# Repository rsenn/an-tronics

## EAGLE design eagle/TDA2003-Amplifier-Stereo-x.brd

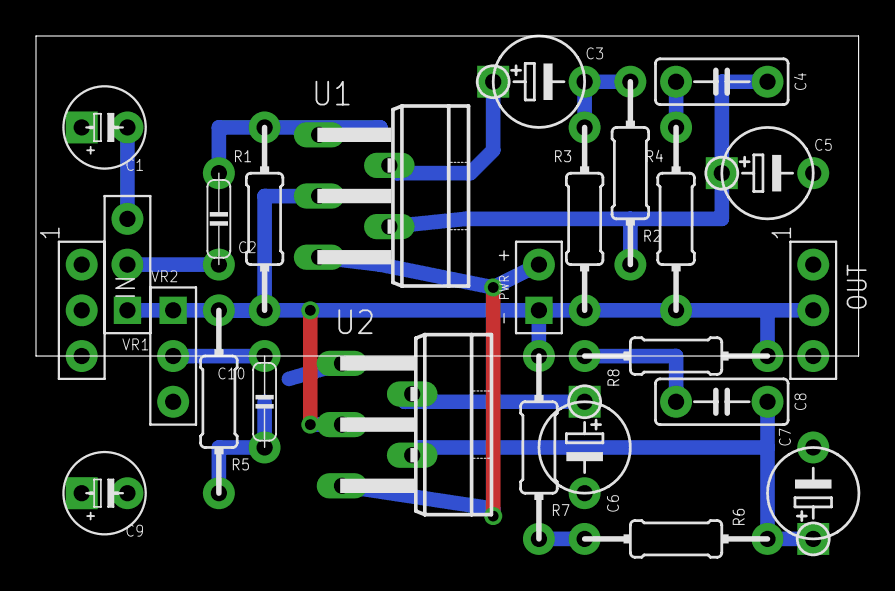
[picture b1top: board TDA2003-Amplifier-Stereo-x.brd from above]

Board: 2 copper layers, 25 parts (0 on the bottom side), 20 nets.

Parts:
C1, C9: 1µF/16V; E2,5-4
C2, C10: 100nF; C050-020X044/V
C3, C6: 220µF/16V; E5-5
C4, C8: 10nF; C050-025X075/V
C5, C7: 1000µF/16V; E5-5
IN: SAUDIO; SPAD-3
OUT: SAUDIO; SPAD-3
PWR: VCC_GNDL; SPAD-+
R1, R5: 100kΩ; 0204/10-V
R2, R6: 220Ω; 0204/10-V
R3, R7: 2.2Ω; 0204/10-V
R4, R8: 1Ω; 0204/10-V
U1, U2: TDA2003-B; TO220-B5
VR1, VR2: 10kΩ; CONN-3P

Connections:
AOUT: C4.1, C5.+, R2.1, U1.4
AOUT1: C7.+, C8.1, R6.1, U2.4
FB: C3.-, R2.2, R3.1
FB1: C6.-, R6.2, R7.1
GND: IN.2, OUT.2, PWR.1, R1.2, R3.2, R4.2, R5.2, R7.2, R8.2, U1.3, U2.3, VR1.1, VR2.1
IN+: C2.2, R1.1, U1.1
IN+1: C10.2, R5.1, U2.1
IN-: C3.+, U1.2
IN-1: C6.+, U2.2
unnamed: C4.2, R4.1
unnamed: C2.1, VR1.2
unnamed: C1.-, VR1.3
unnamed: C1.+, IN.1
unnamed: C8.2, R8.1
unnamed: C9.-, VR2.3
unnamed: C10.1, VR2.2
unnamed: C9.+, IN.3
OUT: C5.-, OUT.1
OUT1: C7.-, OUT.3
VCC: PWR.2, U1.5, U2.5

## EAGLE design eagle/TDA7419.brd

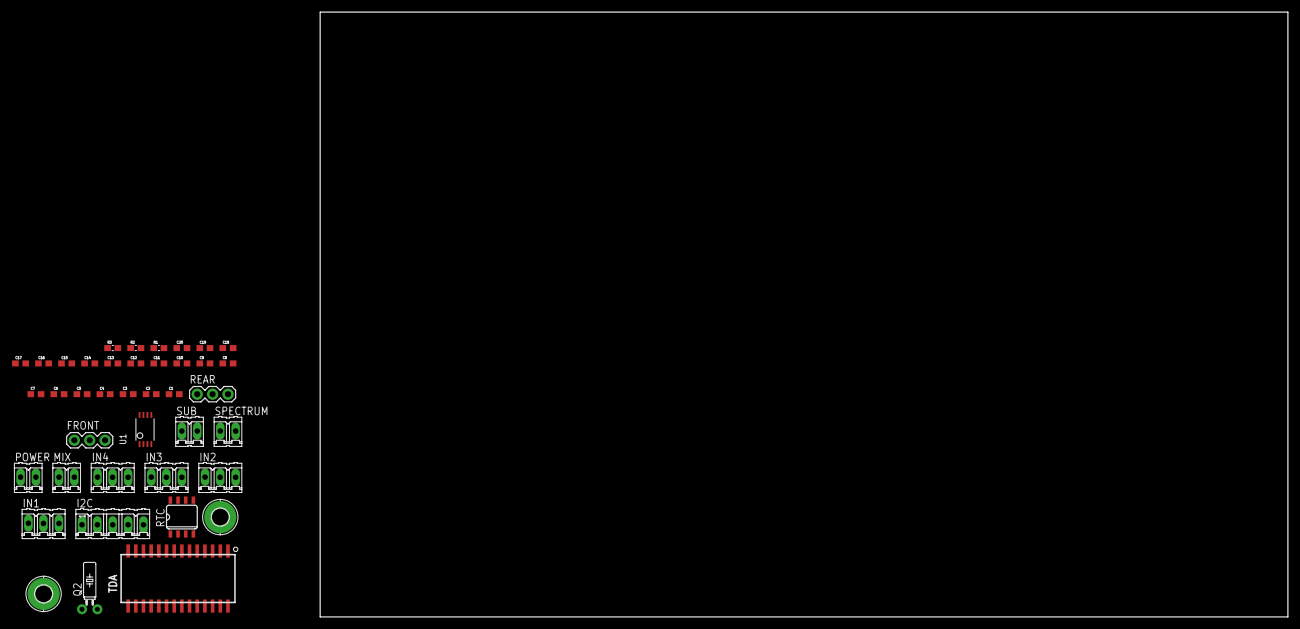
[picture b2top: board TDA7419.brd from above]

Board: 2 copper layers, 160.0 x 100.0 mm, 40 parts (0 on the bottom side), 46 nets, no tracks yet.

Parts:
C1, C13: 10uf; 0603-CAP
C2, C3, C4, C5, C6, C7, C8, C9, C10, C14: 100nf; 0603-CAP
C11, C12: 470nf; 0603-CAP
C15, C16, C17, C18, C19: 4.7uf; 0603-CAP
C20: 8.2pf; 0603-CAP
FRONT: 1X03
H1, H2: MOUNT-PAD-ROUND2.8; 2,8-PAD
I2C: 05P
IN1, IN2, IN3, IN4: 03P
MIX: 02P
POWER: 02P
Q2: TC26HEZ
R1, R2, R3: 10kΩ; 0603-RES
REAR: 1X03
RTC: DS1307SO8-TIGHT; SO08-TIGHT
SPECTRUM: 02P
SUB: 02P
TDA: TDA7419; SOIC-28
U1: TXS0102EPWR; TSSOP8

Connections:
3V3: I2C.4, R1.2, RTC.8, U1.3, U1.7
3VSCL: RTC.6, TDA.22, U1.8
3VSDA: RTC.5, TDA.23, U1.4
5V: I2C.2, R2.2, R3.2, U1.6
5VSCL: I2C.3, R2.1, U1.5
5VSDA: I2C.1, R3.1, U1.1
9V: C13.1, C14.1, C20.1, POWER.1, TDA.24
ACINL: C11.2, TDA.3
ACINR: C12.2, TDA.2
ACOUTL: C11.1, TDA.4
ACOUTR: C12.1, TDA.1
CREF: C1.1, TDA.14
DIFFG: IN4.2, TDA.12
DIFFL: C3.2, TDA.11
DIFFR: C2.2, TDA.13
GND: C1.2, C13.2, C14.2, C20.2, FRONT.2, H1.B2,8, H2.B2,8, I2C.5, IN1.2, IN2.2, IN3.2, MIX.2, POWER.2, R1.1, REAR.2, RTC.3, RTC.4, SUB.2, TDA.15, TDA.27, U1.2
MIX: C10.2, TDA.28
unnamed: C10.1, MIX.1
unnamed: C9.1, IN3.3
unnamed: C8.1, IN3.1
unnamed: C7.1, IN2.3
unnamed: C6.1, IN2.1
unnamed: C5.1, IN1.3
unnamed: C4.1, IN1.1
unnamed: C3.1, IN4.3
unnamed: C2.1, IN4.1
unnamed: C18.1, FRONT.1
unnamed: C17.1, FRONT.3
unnamed: C16.1, REAR.1
unnamed: C15.1, REAR.3
unnamed: C19.1, SUB.1
unnamed: Q2.2, RTC.2
unnamed: Q2.1, RTC.1
OUTLF: C17.2, TDA.20
OUTLR: C15.2, TDA.19
OUTRF: C18.2, TDA.17
OUTRR: C16.2, TDA.18
OUTSW: C19.2, TDA.16
SACLK: SPECTRUM.1, TDA.25
SAOUT: SPECTRUM.2, TDA.26
SE1L: C5.2, TDA.9
SE1R: C4.2, TDA.10
SE2L: C7.2, TDA.7
SE2R: C6.2, TDA.8
SE3L: C9.2, TDA.5
SE3R: C8.2, TDA.6

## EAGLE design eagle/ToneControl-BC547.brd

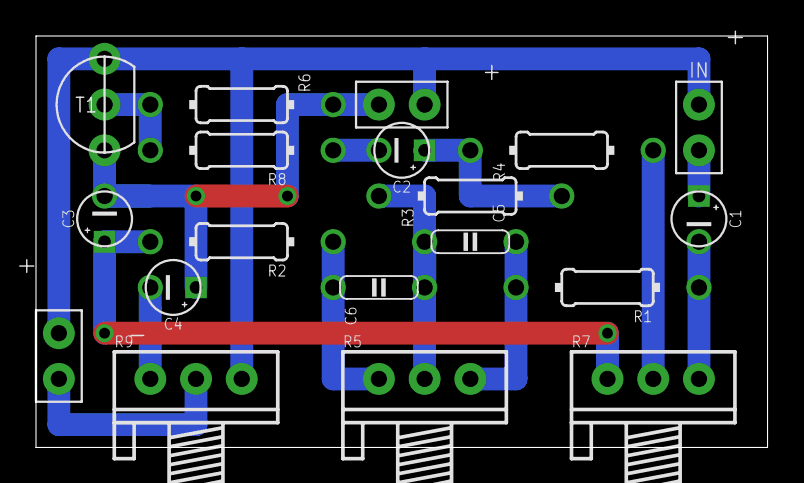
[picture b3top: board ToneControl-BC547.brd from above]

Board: 2 copper layers, 40.6 x 22.9 mm, 19 parts (0 on the bottom side), 14 nets.

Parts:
C1, C3, C4: 3.3μF; E2,5-3
C2: E2,5-3
C5, C6: 100nF; C050-020X044/V
IN: SPAD-+
OUT: SPAD+-
R1, R2: 4.7kΩ; 0204/10
R3: 2.2kΩ; 0204/10-V
R4: 1kΩ; 0204/10-V
R5, R7: 100kΩ; POT
R6: 330kΩ; 0204/10-V
R8: 1kΩ; 0204/10
R9: 20kΩ; POT
S1: VCC_GNDR; SPAD+-
T1: BC547; TO92-CBE

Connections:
GND: IN.1, OUT.1, R9.E, S1.1, T1.E
unnamed: C5.1, R1.2, R5.E
unnamed: C6.1, R2.1, R5.A
unnamed: C5.2, C6.2, R3.1, R5.S
unnamed: C2.+, R3.2, R4.1
unnamed: R4.2, R7.S
unnamed: C2.-, R8.1
unnamed: C3.+, R2.2, R7.A
unnamed: R6.2, R8.2, T1.B
unnamed: C4.-, R9.A
unnamed: C1.-, R1.1, R7.E
unnamed: C1.+, IN.2
unnamed: OUT.2, R9.S
VCC: C3.-, C4.+, R6.1, S1.2, T1.C

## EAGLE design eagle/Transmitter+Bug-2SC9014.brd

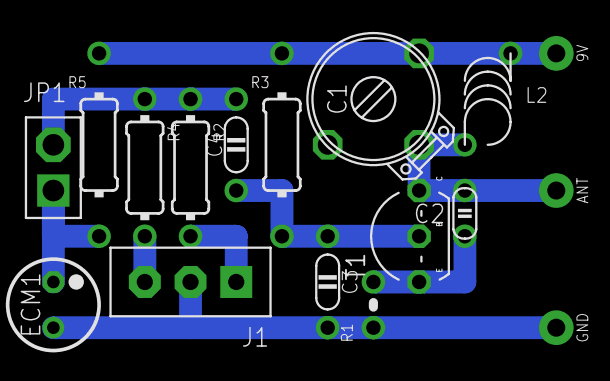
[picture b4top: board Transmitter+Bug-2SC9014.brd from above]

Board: 2 copper layers, 17 parts (0 on the bottom side), 9 nets.

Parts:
9V: SPAD
ANT: ANT; SPAD
C1: 1.6-15pF; TRIM-2222-808
C2: 4.7pF; C025-015X024
C3: 1nF; C050-020X036/V
C4: 10nF; C050-020X036/V
ECM1: ECM-5
GND: SPAD
J1: CONN-3P-3P; CONN-3P
JP1: CONN-2P2P/V; CONN-2P-V
L2: 1uH; L-04-2/5V-X
R1: 100; 0204/2V
R2, R4: 47k; 0204/7-V
R3: 10k; 0204/10-V
R5: 4.7k; 0204/10-V
T1: 2SC9014; TO92-EBC

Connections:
+UB: 9V.1, C1.3, L2.1, R3.1, R5.1
GND: C3.2, ECM1.2, GND.1, J1.2, R1.1
unnamed: J1.3, R4.1
unnamed: ANT.1, C1.2, C2.1, L2.2, T1.C
unnamed: C2.2, R1.2, T1.E
unnamed: J1.1, R2.1
unnamed: C3.1, C4.1, R3.2, T1.B
unnamed: C4.2, JP1.2, R2.2, R4.2
unnamed: ECM1.1, JP1.1, R5.2

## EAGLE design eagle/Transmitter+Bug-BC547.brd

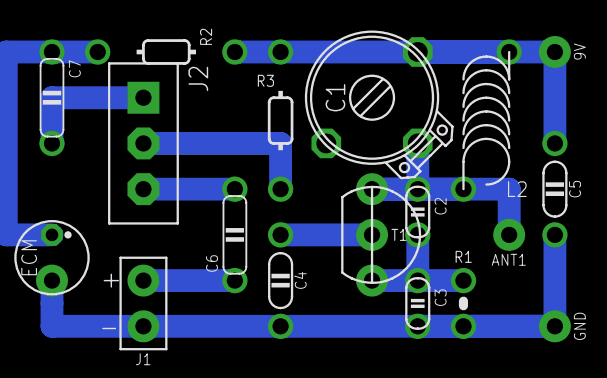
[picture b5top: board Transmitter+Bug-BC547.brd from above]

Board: 2 copper layers, 18 parts (0 on the bottom side), 9 nets.

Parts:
9V: SPAD
ANT1: ANT; SPAD
C1: 1.6-15pF; TRIM-2222-808
C2: 4.7pF; C025-015X024
C3: 1nF; C025-015X024
C4: 1nF; C050-020X036/V
C5: 22nF; C050-020X036/V
C6, C7: 330nF; C050-020X044
ECM: ECM-4
GND: SPAD
J1: SPAD-+
J2: CONN-3P
L2: 1μH; L-04/7V-X
R1: 4.7Ω; 0204/2V
R2: 4.7kΩ; 0202/7-V
R3: 33kΩ; 0202/7-V
T1: BC547; TO92-CBE

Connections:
+UB: 9V.1, C1.3, C5.1, L2.2, R2.1, R3.1
GND: C3.2, C4.2, C5.2, ECM.2, GND.1, J1.1, R1.2
MOD: C4.1, J2.2, R3.2, T1.B
unnamed: C6.2, J2.3
unnamed: ANT1.1, C1.2, C2.1, L2.1, T1.C
unnamed: C2.2, C3.1, R1.1, T1.E
unnamed: C7.2, J2.1
unnamed: C6.1, J1.2
unnamed: C7.1, ECM.1, R2.2

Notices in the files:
parts and their libraries:
SparkFun-Connectors: Licensing: CC v3.0 Share-Alike You are welcome to use this library for commercial purposes.
SparkFun-FreqCtrl: Licensing: Creative Commons ShareAlike 4.0 International - https://creativecommons.org/licenses/by-sa/4.0
